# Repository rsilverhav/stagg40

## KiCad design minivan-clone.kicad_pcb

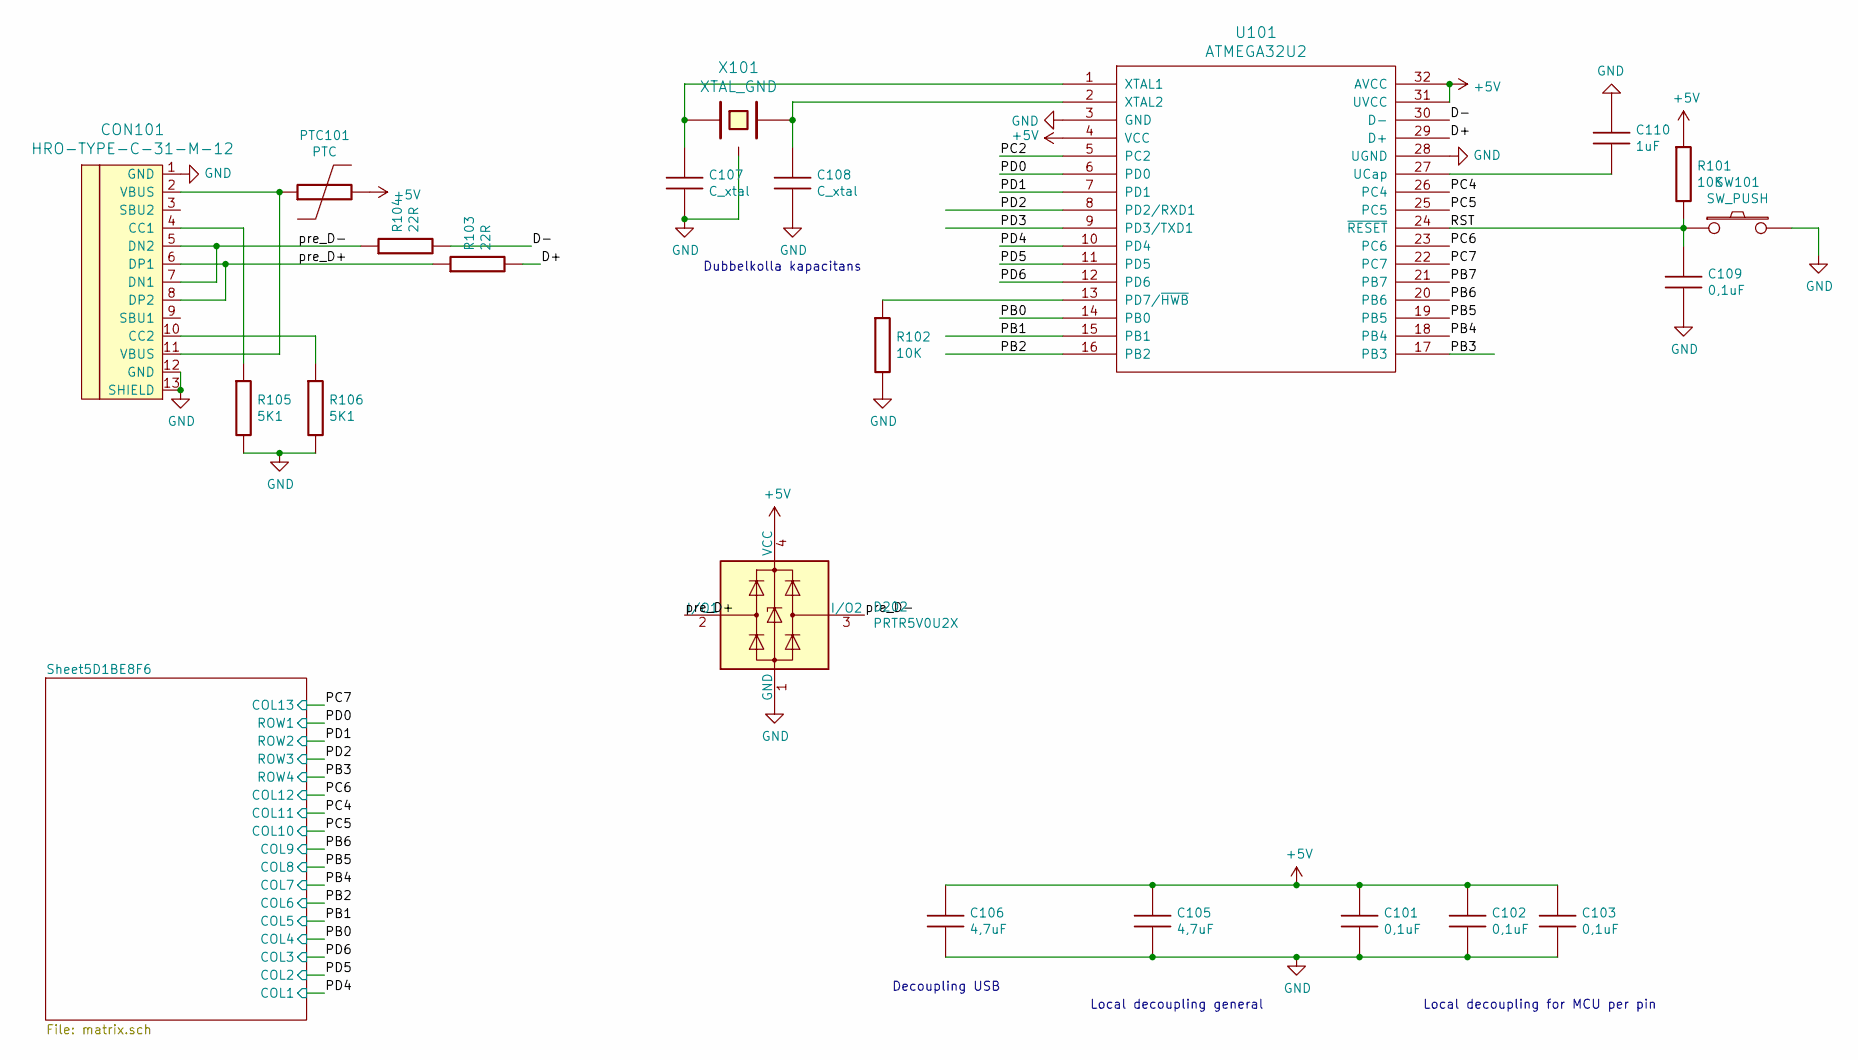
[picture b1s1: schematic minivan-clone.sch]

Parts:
C101, C102, C103, C109: 0,1uF; C_1608_rev2
C105, C106: 4,7uF; C_3216_rev2
C107, C108: C_xtal; C_1608_rev2
C110: 1uF; C_3216_rev2
CON101: HRO-TYPE-C-31-M-12; HRO-TYPE-C-31-M-12-HandSoldering
D202: PRTR5V0U2X; SOT-143
PTC101: PTC; C_3216_rev2
R101, R102: 10K; R_1608_rev2
R103, R104: 22R; R_1608_rev2
R105, R106: 5K1; R_1608_rev2
SW101: SW_PUSH; SW_ALPS_SKRP
U101: ATMEGA32U2; QFP32
X101: XTAL_GND; FA-238

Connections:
+5V: C101.1, C102.1, C103.1, C105.1, C106.1, D202.4 (VCC), PTC101.2, R101.1, U101.4 (VCC), U101.31 (UVCC), U101.32 (AVCC)
/D+: R103.2, U101.29 (D+)
/D-: R104.2, U101.30 (D-)
/PB0: U101.14 (PB0); also elsewhere on the board
/PB1: U101.15 (PB1); also elsewhere on the board
/PB2: U101.16 (PB2); also elsewhere on the board
/PB3: U101.17 (PB3); also elsewhere on the board
/PB4: U101.18 (PB4); also elsewhere on the board
/PB5: U101.19 (PB5); also elsewhere on the board
/PB6: U101.20 (PB6); also elsewhere on the board
/PB7: U101.21 (PB7)
/PC2: U101.5 (PC2)
/PC4: U101.26 (PC4); also elsewhere on the board
/PC5: U101.25 (PC5); also elsewhere on the board
/PC6: U101.23 (PC6); also elsewhere on the board
/PC7: U101.22 (PC7); also elsewhere on the board
/PD0: U101.6 (PD0); also elsewhere on the board
/PD1: U101.7 (PD1); also elsewhere on the board
/PD2: U101.8 (PD2/RXD1); also elsewhere on the board
/PD3: U101.9 (PD3/TXD1)
/PD4: U101.10 (PD4); also elsewhere on the board
/PD5: U101.11 (PD5); also elsewhere on the board
/PD6: U101.12 (PD6); also elsewhere on the board
/RST: C109.1, R101.2, SW101.1, U101.24 (~RESET)
/pre_D+: CON101.6 (DP1), CON101.8 (DP2), D202.2 (I/O1), R103.1
/pre_D-: CON101.5 (DN2), CON101.7 (DN1), D202.3 (I/O2), R104.1
GND: C101.2, C102.2, C103.2, C105.2, C106.2, C107.2, C108.2, C109.2, C110.1, CON101.1 (GND), CON101.12 (GND), CON101.13 (SHIELD), D202.1 (GND), R102.2, R105.2, R106.2, SW101.2, U101.3 (GND), U101.28 (UGND), X101.3
unnamed: C107.1, U101.1 (XTAL1), X101.1
unnamed: C108.1, U101.2 (XTAL2), X101.2
unnamed: C110.2, U101.27 (UCap)
unnamed: CON101.4 (CC1), R105.1
unnamed: CON101.10 (CC2), R106.1
unnamed: CON101.2 (VBUS), CON101.11 (VBUS), PTC101.1
unnamed: R102.1, U101.13 (PD7/~HWB)

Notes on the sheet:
Local decoupling for MCU per pin
Local decoupling general
Decoupling USB
Dubbelkolla kapacitans

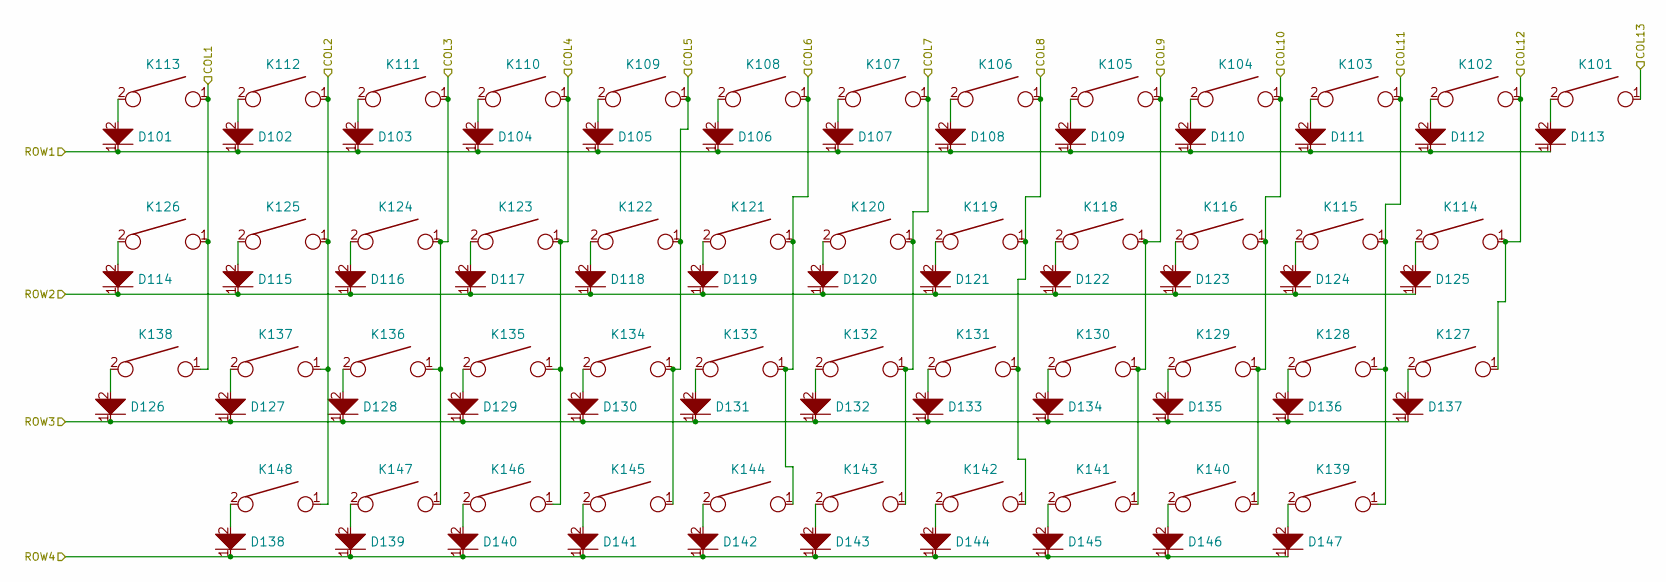
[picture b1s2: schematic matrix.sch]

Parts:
D101, D102, D103, D104, D105, D106, D107, D108, D109, D110, D111, D112, D113, D114, D115, D116, D117, D118, D119, D120, D121, D122, D123, D124, D125, D126, D127, D128, D129, D130, D131, D132, D133, D134, D135, D136, D137, D138, D139, D140, D141, D142, D143, D144, D145, D146, D147: D; D_SC79
K101, K102, K103, K104, K105, K106, K107, K108, K109, K110, K111, K112, K113, K114, K115, K116, K118, K119, K120, K121, K122, K123, K124, K125, K126, K127, K128, K129, K130, K131, K132, K133, K134, K135, K136, K137, K138, K139, K140, K141, K142, K143, K144, K145, K146, K147, K148: KEYSW; Mx_Alps_100

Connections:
/PB0: K110.1, K123.1, K135.1, K146.1; also elsewhere on the board
/PB1: K109.1, K122.1, K134.1, K145.1; also elsewhere on the board
/PB2: K108.1, K121.1, K133.1, K144.1; also elsewhere on the board
/PB3: D138.1, D139.1, D140.1, D141.1, D142.1, D143.1, D144.1, D145.1, D146.1, D147.1; also elsewhere on the board
/PB4: K107.1, K120.1, K132.1, K143.1; also elsewhere on the board
/PB5: K106.1, K119.1, K131.1, K142.1; also elsewhere on the board
/PB6: K105.1, K118.1, K130.1, K141.1; also elsewhere on the board
/PC4: K103.1, K115.1, K128.1, K139.1; also elsewhere on the board
/PC5: K104.1, K116.1, K129.1, K140.1; also elsewhere on the board
/PC6: K102.1, K114.1, K127.1; also elsewhere on the board
/PC7: K101.1; also elsewhere on the board
/PD0: D101.1, D102.1, D103.1, D104.1, D105.1, D106.1, D107.1, D108.1, D109.1, D110.1, D111.1, D112.1, D113.1; also elsewhere on the board
/PD1: D114.1, D115.1, D116.1, D117.1, D118.1, D119.1, D120.1, D121.1, D122.1, D123.1, D124.1, D125.1; also elsewhere on the board
/PD2: D126.1, D127.1, D128.1, D129.1, D130.1, D131.1, D132.1, D133.1, D134.1, D135.1, D136.1, D137.1; also elsewhere on the board
/PD4: K113.1, K126.1, K138.1; also elsewhere on the board
/PD5: K112.1, K125.1, K137.1, K148.1; also elsewhere on the board
/PD6: K111.1, K124.1, K136.1, K147.1; also elsewhere on the board
unnamed 35: D101.2, K113.2; also elsewhere on the board
unnamed: D102.2, K112.2
unnamed: D103.2, K111.2
unnamed: D104.2, K110.2
unnamed: D105.2, K109.2
unnamed: D106.2, K108.2
unnamed: D107.2, K107.2
unnamed: D108.2, K106.2
unnamed: D109.2, K105.2
unnamed: D110.2, K104.2
unnamed: D111.2, K103.2
unnamed: D112.2, K102.2
unnamed: D113.2, K101.2
unnamed: D114.2, K126.2
unnamed: D115.2, K125.2
unnamed: D116.2, K124.2
unnamed: D117.2, K123.2
unnamed: D118.2, K122.2
unnamed: D119.2, K121.2
unnamed: D120.2, K120.2
unnamed: D121.2, K119.2
unnamed: D122.2, K118.2
unnamed: D123.2, K116.2
unnamed: D124.2, K115.2
unnamed: D125.2, K114.2
unnamed: D126.2, K138.2
unnamed: D127.2, K137.2
unnamed: D128.2, K136.2
unnamed: D129.2, K135.2
unnamed: D130.2, K134.2
unnamed: D131.2, K133.2
unnamed: D132.2, K132.2
unnamed: D133.2, K131.2
unnamed: D134.2, K130.2
unnamed: D135.2, K129.2
unnamed: D136.2, K128.2
unnamed: D137.2, K127.2
unnamed: D138.2, K148.2
unnamed: D139.2, K147.2
unnamed: D140.2, K146.2
unnamed: D141.2, K145.2
unnamed: D142.2, K144.2
unnamed: D143.2, K143.2
unnamed: D144.2, K142.2
unnamed: D145.2, K141.2
unnamed: D146.2, K140.2
unnamed: D147.2, K139.2

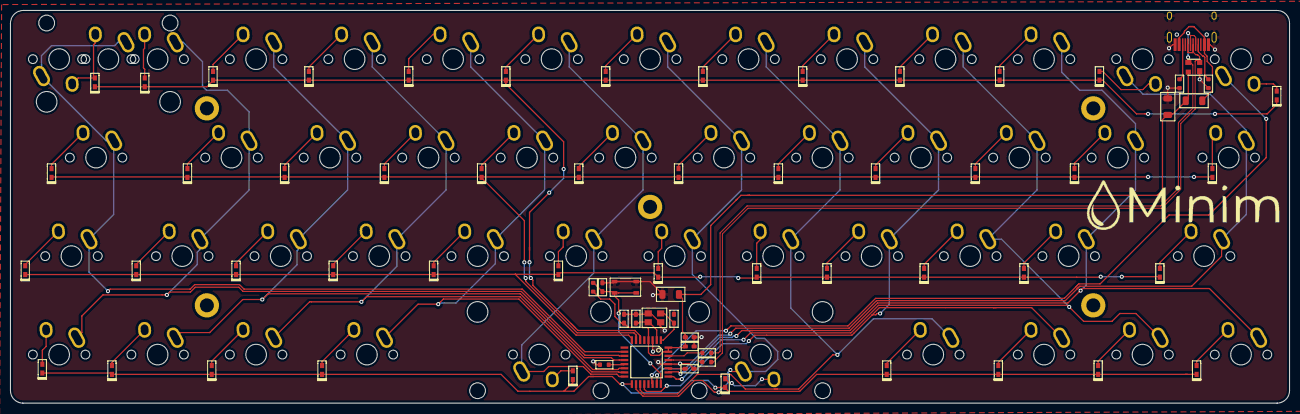
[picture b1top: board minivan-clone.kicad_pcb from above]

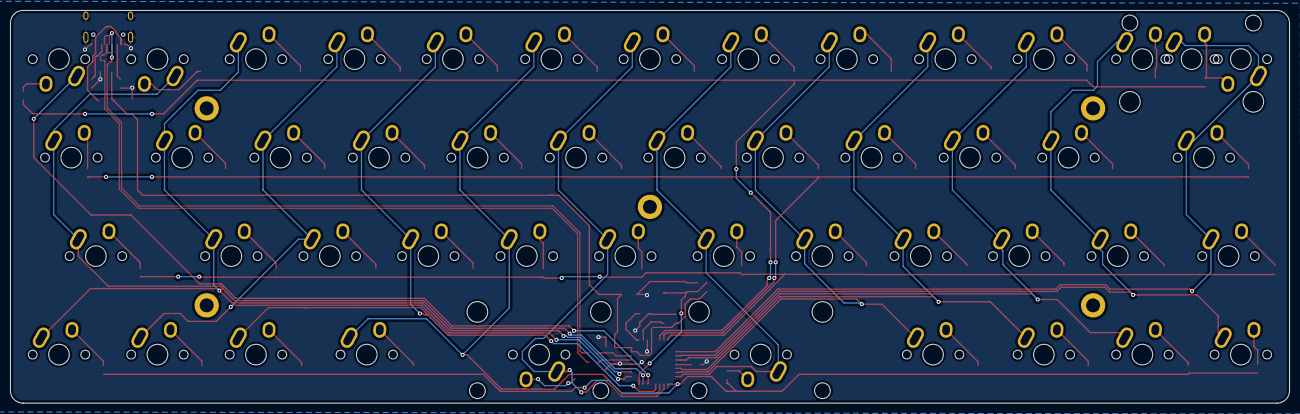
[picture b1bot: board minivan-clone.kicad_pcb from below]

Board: 2 copper layers, 247.4 x 75.9 mm, 121 parts (48 on the bottom side), 78 nets.

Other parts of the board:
>NAME: >VALUE; Mx_Alps_200
H1, H2, H3, H4, H5: MountingHole_2.7mm_M2.5_DIN965_Pad

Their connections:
/PD4: >NAME.1; also elsewhere on the board
unnamed 35: >NAME.2; also elsewhere on the board

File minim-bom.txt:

"Source:","/Users/robin/dev/keyboard/stagg40/minivan-clone.sch"
"Date:","2019 September 12, Thursday 15:38:11"
"Tool:","Eeschema (5.1.4-0-10_14)"
"Generator:","/private/var/folders/__/z2sclncd0xdb_vw218gs_dxr0000gn/T/AppTranslocation/F8DCCDFE-146E-4836-AE0A-B33FDACCE663/d/kicad.app/Contents/SharedSupport/plugins/bom_csv_grouped_by_value_with_fp.py"
"Component Count:","115"
"Ref","Qnty","Value","Cmp name","Footprint","Description","Vendor"
"C102, C101, C103, C109, ","4","0,1uF","C","keyboard_parts:C_1608_rev2","",""
"C105, C106, ","2","4,7uF","C","keyboard_parts:C_3216_rev2","",""
"C107, C108, ","2","C_xtal","C","keyboard_parts:C_1608_rev2","",""
"C110, ","1","1uF","C","keyboard_parts:C_3216_rev2","",""
"CON101, ","1","HRO-TYPE-C-31-M-12","HRO-TYPE-C-31-M-12-Type-C-minivan-clone-rescue-minivan-clone-rescue","Type-C:HRO-TYPE-C-31-M-12-HandSoldering","",""
"D101, D102, D103, D104, D105, D106, D107, D108, D109, D110, D111, D112, D117, D118, D119, D114, D115, D116, D120, D121, D122, D123, D124, D125, D129, D130, D131, D126, D127, D128, D132, D133, D134, D135, D136, D137, D141, D142, D143, D138, D139, D140, D144, D145, D146, D147, D113, ","47","D","D","keyboard_parts:D_SC79","",""
"D202, ","1","PRTR5V0U2X","PRTR5V0U2X","Package_TO_SOT_SMD:SOT-143","Ultra low capacitance double rail-to-rail ESD protection diode, SOT-363",""
"K101, K102, K103, K104, K105, K106, K107, K108, K110, K111, K112, K113, K118, K119, K120, K115, K116, K117, K121, K122, K123, K124, K125, K126, K130, K131, K132, K127, K128, K129, K133, K134, K135, K136, K137, K138, K142, K143, K144, K139, K140, K141, K145, K146, K147, K148, K114, ","47","KEYSW","KEYSW","keebs:Mx_Alps_100","",""
"PTC101, ","1","PTC","PTC","keyboard_parts:C_3216_rev2","",""
"R101, R102, ","2","10K","R","keyboard_parts:R_1608_rev2","",""
"R104, R103, ","2","22R","R","keyboard_parts:R_1608_rev2","",""
"R106, R105, ","2","5K1","R","keyboard_parts:R_1608_rev2","",""
"SW101, ","1","SW_PUSH","SW_PUSH","keyboard_parts:SW_ALPS_SKRP","",""
"U101, ","1","ATMEGA32U2","ATMEGA32U2","keyboard_parts:QFP32","",""
"X101, ","1","XTAL_GND","XTAL_GND","keyboard_parts:FA-238","",""

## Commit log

2019-07-02 initial commit
    initial commit
2019-07-04 done work on mcu and started on matrix
    done work on mcu and started on matrix
2019-07-05 started doing layout
    started doing layout
2019-08-12 started layout
    started layout
2019-08-16 fixed row 2
2019-08-30 added -bak and -rescue* to gitignore
2019-08-30 removed cache and backup files
2019-08-30 placed all connected diods
2019-09-02 added missing connections for diods, diods on pcb
2019-09-02 removed ICSP, fixed gnd and 5v
2019-09-02 placed processor and usb components
2019-09-03 Started routing
    Started routing
2019-09-05 fixed pour
    fixed pour
2019-09-05 aligned bottom row keys
2019-09-11 added icon to pcb
2019-09-12 added mounting holes
2019-09-12 fixed DRC errors
2019-09-12 added gerber files and component list
2019-09-15 started mirroring keyboard layout
2019-09-16 fixed staggering, rotated cpu, removed all tracks, started redoing tracks
2019-09-16 started adding tracks
2019-09-16 more tracks for leftmost cols
2019-09-17 more tracks
2019-09-17 done with tracks for leftmost cols
2019-09-17 tracks for all leftmost rows, started with rightmost cols
2019-09-17 added all tracks
2019-09-17 fixed fills
2019-09-17 fixed logo in silk
2019-09-18 modified some footprints, removing outlines and references
2019-09-18 Mirroring layout
2019-09-18 updated gerber files with mirrored layout
2019-09-18 moved tracks at bottom of pcb, regenerated gerber
2019-09-28 moved all switches to the back of the board, rotated then 180 deg
2019-09-28 fixed DRC errors and fixed some tracks too close to the edge of the PCB
2019-09-30 fixed texts
2019-09-30 rotated 90deg switch to have same rotation as others, added pads on mounting holes
2019-09-30 updated gerber files for rev2
2020-02-25 swapped incorrect - and + for usb
2020-02-26 added kicad_pcb file for plate, created footprints for cutouts
2020-02-26 plate has increased size with 6mm
2020-02-27 increased plate to 8mm extra
2020-03-31 added soldering mask around cutout
2020-04-01 fixed soldering mask for 225, fixed placement of m3
2020-04-01 generated gerber files for plate top
2020-04-02 moved cutouts for switches to Edge.Cuts
2020-04-02 missed files
2020-04-02 fixed minor issue with line too close to pad, updated rev text to 3, regenerated gerber
2020-04-02 added plate bot, generated gerber
2020-11-30 centered screws for plates, regenerated gerber files
